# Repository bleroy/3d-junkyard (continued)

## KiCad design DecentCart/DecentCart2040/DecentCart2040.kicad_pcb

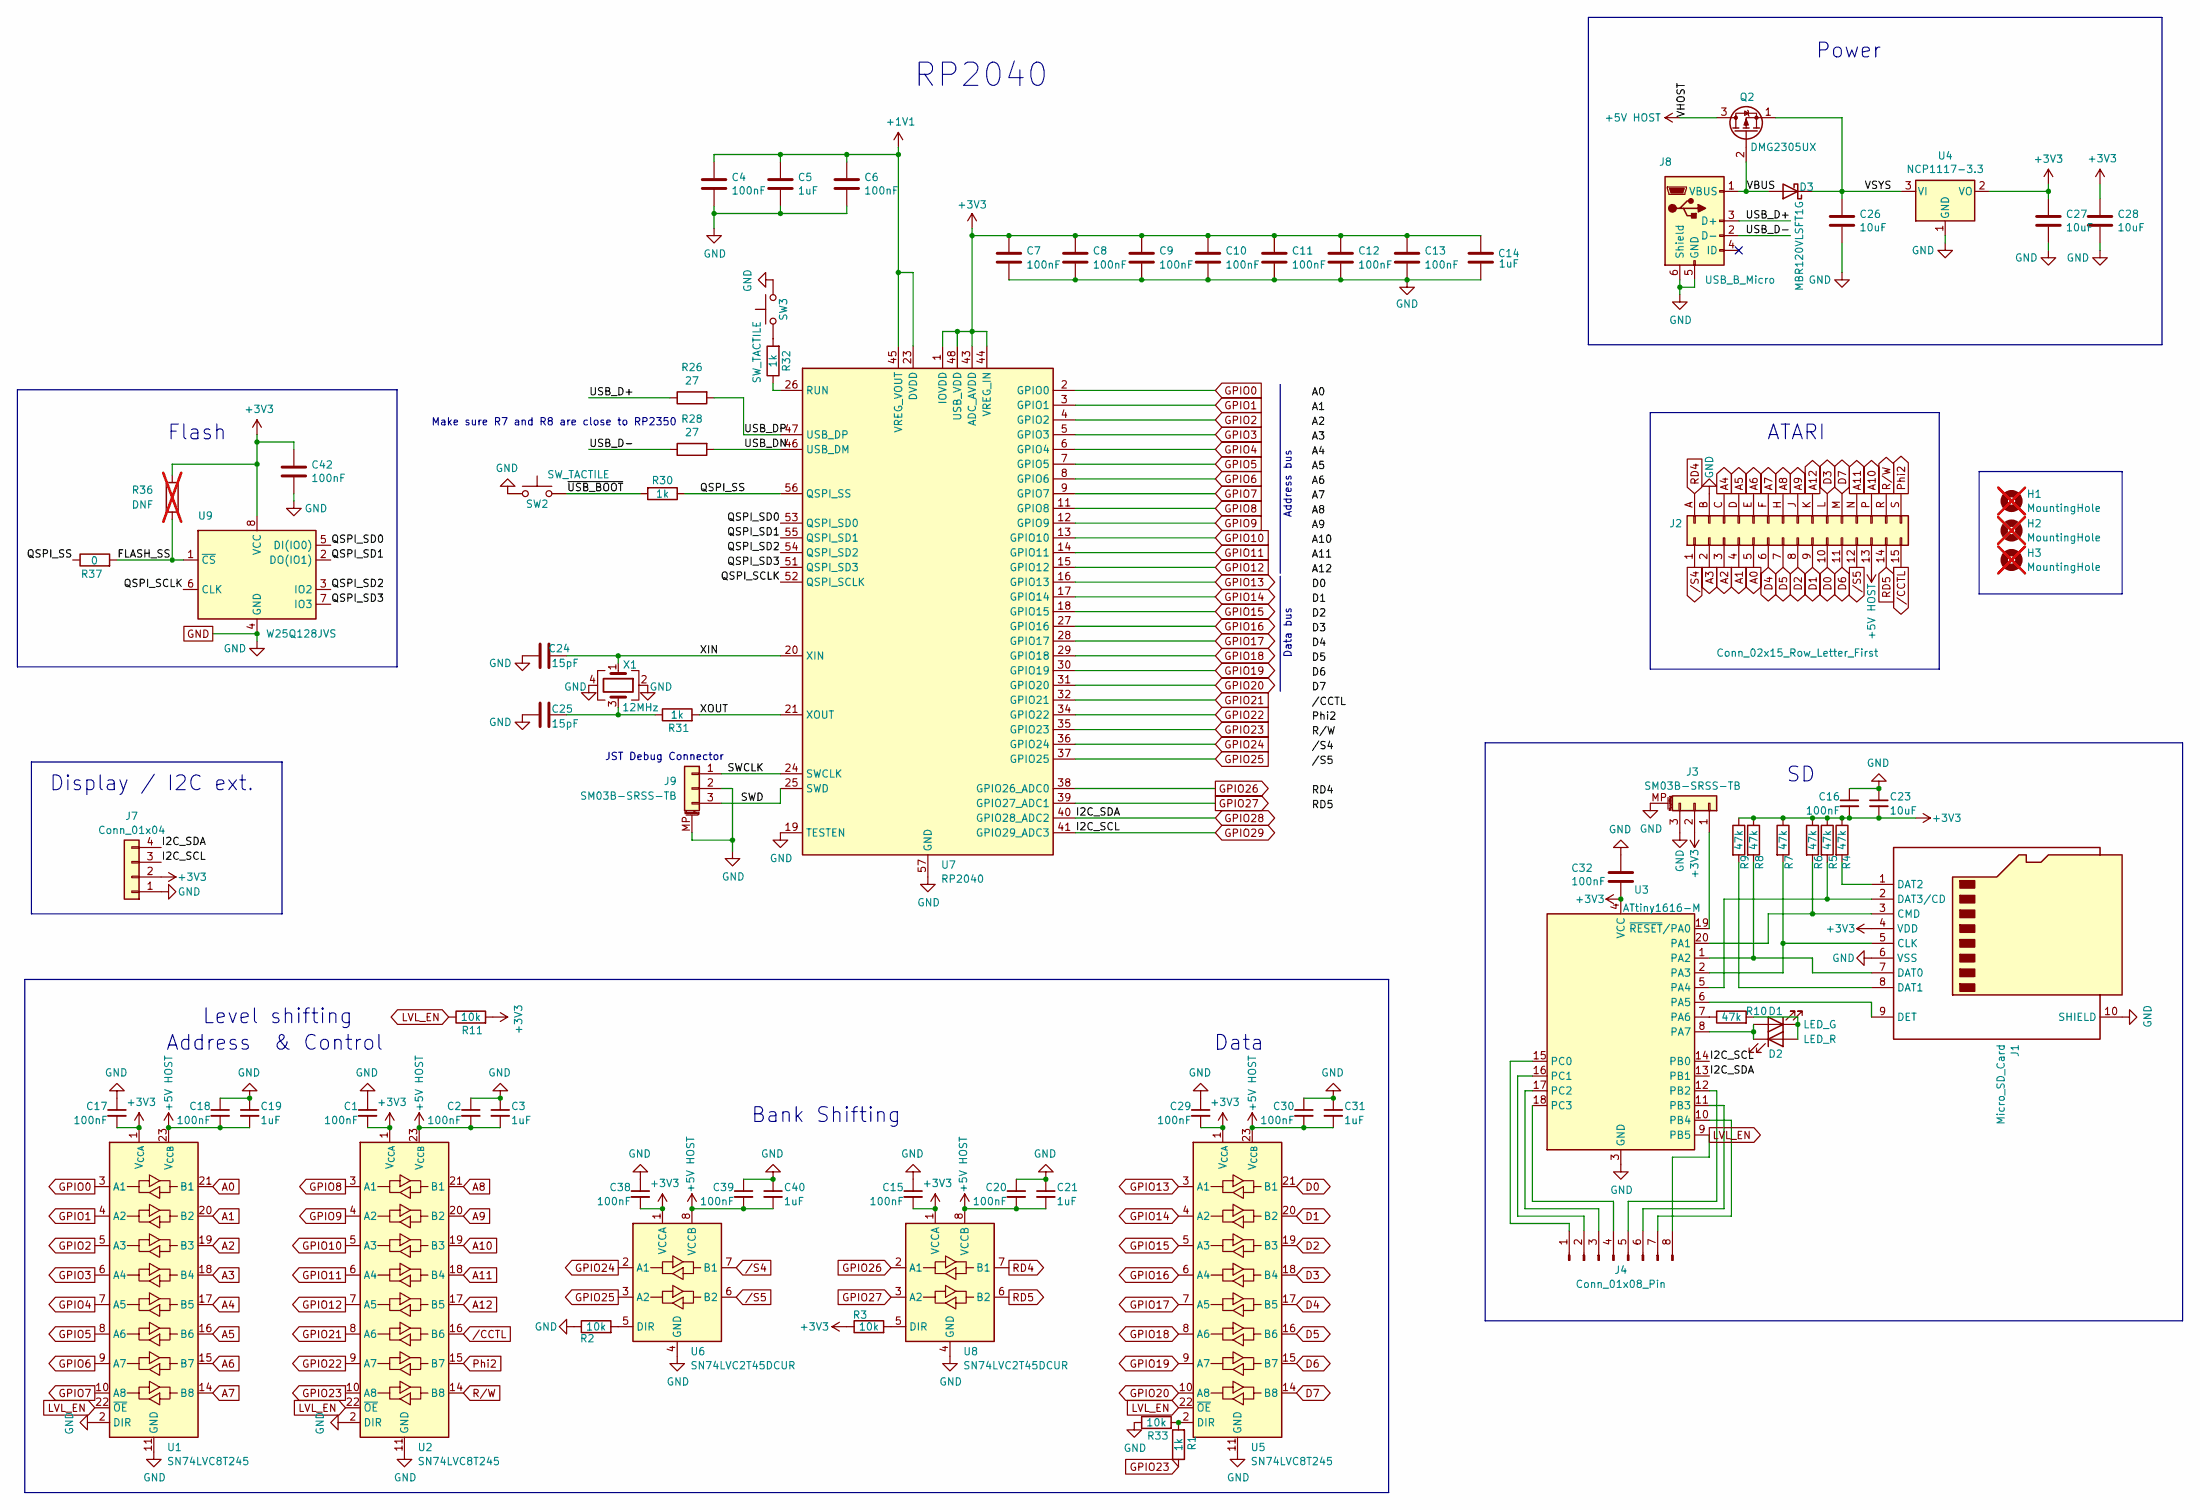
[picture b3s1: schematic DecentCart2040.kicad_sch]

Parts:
C1, C2, C4, C6, C7, C8, C9, C10, C11, C12, C13, C15, C16, C17, C18, C20, C29, C30, C32, C38, C39, C42: 100nF; C_0402_1005Metric; JLCPCB Part # C1525
C3, C5, C14, C19, C21, C31, C40: 1uF; C_0402_1005Metric; JLCPCB Part # C52923
C23, C26, C27, C28: 10uF; C_0402_1005Metric; JLCPCB Part # C15525
C24, C25: 15pF; C_0402_1005Metric; JLCPCB Part # C1548
D1: LED_G; LED_0805_2012Metric; JLCPCB Part # C2297
D2: LED_R; LED_0603_1608Metric; JLCPCB Part # C2286
D3: MBR120VLSFT1G; Nexperia_CFP3_SOD-123W; JLCPCB Part # C223608
H1, H2, H3: MountingHole; MountingHole_2.2mm_M2; not fitted
J1: Micro_SD_Card; Micro SD; JLCPCB Part # C20613191
J2: Conn_02x15_Row_Letter_First; Atari Cartridge Edge Connector
J3, J9: SM03B-SRSS-TB; JST_SH_BM03B-SRSS-TB_1x03-1MP_P1.00mm_Vertical; JLCPCB Part # C160389
J4: Conn_01x08_Pin; PinHeader_2x04_P1.27mm_Vertical
J7: Conn_01x04; OLED_modeule_0_91_128x32_I2C
J8: USB_B_Micro; USB_Micro-B; JLCPCB Part # C2765187
Q2: DMG2305UX; SOT-23; JLCPCB Part # C150470
R1, R30, R31, R32: 1k; R_0402_1005Metric; JLCPCB Part # C11702
R2, R3, R11, R33: 10k; R_0402_1005Metric; JLCPCB Part # C25744
R4, R5, R6, R7, R8, R9, R10: 47k; R_0402_1005Metric; JLCPCB Part # C25792
R26, R28: 27; R_0805_2012Metric; JLCPCB Part # C17561
R36: DNF; R_0402_1005Metric; not fitted
R37: 0; SolderJumper-2_P1.3mm_Bridged_RoundedPad1.0x1.5mm; JLCPCB Part # C2074089
SW2, SW3: SW_TACTILE; Tactile_Switch_Basic_XKB_TS-1187A; JLCPCB Part # C318884
U1, U2, U5: SN74LVC8T245; TSSOP-24_4.4x7.8mm_P0.65mm; JLCPCB Part # C27643
U3: ATtiny1616-M; VQFN-20-1EP_3x3mm_P0.4mm_EP1.7x1.7mm; JLCPCB Part # C507118
U4: NCP1117-3.3; SOT-223-3_TabPin2; JLCPCB Part # C6186
U6, U8: SN74LVC2T45DCUR; VSSOP-8_2.3x2mm_P0.5mm; JLCPCB Part # C15741
U7: RP2040; QFN-56-1EP_7x7mm_P0.4mm_EP3.2x3.2mm; JLCPCB Part # C2040
U9: W25Q128JVS; SOIC-8_5.23x5.23mm_P1.27mm; JLCPCB Part # C97521
X1: 12MHz; Crystal_SMD_Abracon_ABM8AIG-4Pin_3.2x2.5mm; JLCPCB Part # C9002

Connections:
+1V1: C4.1, C5.1, C6.1, U7.23 (DVDD), U7.45 (VREG_VOUT), U7.50 (DVDD)
+3V3: C1.2, C7.1, C8.1, C9.1, C10.1, C11.1, C12.1, C13.1, C14.1, C15.2, C16.2, C17.2, C23.2, C27.1, C28.1, C29.2, C32.2, C38.2, C42.1, J1.4 (VDD), J3.2, J7.2, R3.1, R4.1, R5.1, R6.1, R7.1, R8.1, R9.1, R11.2, R36.1, U1.1 (V_{CCA}), U2.1 (V_{CCA}), U3.4 (VCC), U4.2 (VO), U5.1 (V_{CCA}), U6.1 (VCCA), U7.1 (IOVDD), U7.10 (IOVDD), U7.22 (IOVDD), U7.33 (IOVDD), U7.42 (IOVDD), U7.43 (ADC_AVDD), U7.44 (VREG_IN), U7.48 (USB_VDD), U7.49 (IOVDD), U8.1 (VCCA), U9.8 (VCC)
+5V HOST: C2.2, C3.2, C18.2, C19.2, C20.2, C21.2, C30.2, C31.2, C39.2, C40.2, J2.13, Q2.3 (D), U1.23 (V_{CCB}), U1.24 (V_{CCB}), U2.23 (V_{CCB}), U2.24 (V_{CCB}), U5.23 (V_{CCB}), U5.24 (V_{CCB}), U6.8 (VCCB), U8.8 (VCCB)
/FLASH_SS: R36.2, R37.2, U9.1 (~CS)
/QSPI_SCLK: U7.52 (QSPI_SCLK), U9.6 (CLK)
/QSPI_SD0: U7.53 (QSPI_SD0), U9.5 (DI(IO0))
/QSPI_SD1: U7.55 (QSPI_SD1), U9.2 (DO(IO1))
/QSPI_SD2: U7.54 (QSPI_SD2), U9.3 (IO2)
/QSPI_SD3: U7.51 (QSPI_SD3), U9.7 (IO3)
/QSPI_SS: R30.1, R37.1, U7.56 (QSPI_SS)
/SWCLK: J9.1, U7.24 (SWCLK)
/SWD: J9.3, U7.25 (SWD)
/USB_D+: J8.3 (D+), R26.1
/USB_D-: J8.2 (D-), R28.1
/USB_DN: R28.2, U7.46 (USB_DM)
/USB_DP: R26.2, U7.47 (USB_DP)
/VBUS: D3.2 (A), J8.1 (VBUS), Q2.2 (G)
/XIN: C24.1, U7.20 (XIN), X1.1
/XOUT: R31.2, U7.21 (XOUT)
/~USB_BOOT: R30.2, SW2.2
A0: J2.5, U1.21 (B1)
A1: J2.4, U1.20 (B2)
A2: J2.3, U1.19 (B3)
A3: J2.2, U1.18 (B4)
A4: J2.C, U1.17 (B5)
A5: J2.D, U1.16 (B6)
A6: J2.E, U1.15 (B7)
A7: J2.F, U1.14 (B8)
A8: J2.H, U2.21 (B1)
A9: J2.J, U2.20 (B2)
A10: J2.P, U2.19 (B3)
A11: J2.N, U2.18 (B4)
A12: J2.K, U2.17 (B5)
D0: J2.10, U5.21 (B1)
D1: J2.9, U5.20 (B2)
D2: J2.8, U5.19 (B3)
D3: J2.L, U5.18 (B4)
D4: J2.6, U5.17 (B5)
D5: J2.7, U5.16 (B6)
D6: J2.11, U5.15 (B7)
D7: J2.M, U5.14 (B8)
GND: C1.1, C2.1, C3.1, C4.2, C5.2, C6.2, C7.2, C8.2, C9.2, C10.2, C11.2, C12.2, C13.2, C14.2, C15.1, C16.1, C17.1, C18.1, C19.1, C20.1, C21.1, C23.1, C24.2, C25.1, C26.2, C27.2, C28.2, C29.1, C30.1, C31.1, C32.1, C38.1, C39.1, C40.1, C42.2, J1.6 (VSS), J1.10 (SHIELD), J2.B, J3.3, J3.MP (MountPin), J7.1, J8.5 (GND), J8.6 (Shield), J9.2, J9.MP (MountPin), R2.1, R33.1, SW2.1, SW3.2, U1.2 (DIR), U1.11 (GND), U1.12 (GND), U1.13 (GND), U2.2 (DIR), U2.11 (GND), U2.12 (GND), U2.13 (GND), U3.3 (GND), U3.21 (GND), U4.1 (GND), U5.11 (GND), U5.12 (GND), U5.13 (GND), U6.4 (GND), U7.19 (TESTEN), U7.57 (GND), U8.4 (GND), U9.4 (GND), X1.2, X1.4
GPIO0: U1.3 (A1), U7.2 (GPIO0)
GPIO1: U1.4 (A2), U7.3 (GPIO1)
GPIO2: U1.5 (A3), U7.4 (GPIO2)
GPIO3: U1.6 (A4), U7.5 (GPIO3)
GPIO4: U1.7 (A5), U7.6 (GPIO4)
GPIO5: U1.8 (A6), U7.7 (GPIO5)
GPIO6: U1.9 (A7), U7.8 (GPIO6)
GPIO7: U1.10 (A8), U7.9 (GPIO7)
GPIO8: U2.3 (A1), U7.11 (GPIO8)
GPIO9: U2.4 (A2), U7.12 (GPIO9)
GPIO10: U2.5 (A3), U7.13 (GPIO10)
GPIO11: U2.6 (A4), U7.14 (GPIO11)
GPIO12: U2.7 (A5), U7.15 (GPIO12)
GPIO13: U5.3 (A1), U7.16 (GPIO13)
GPIO14: U5.4 (A2), U7.17 (GPIO14)
GPIO15: U5.5 (A3), U7.18 (GPIO15)
GPIO16: U5.6 (A4), U7.27 (GPIO16)
GPIO17: U5.7 (A5), U7.28 (GPIO17)
GPIO18: U5.8 (A6), U7.29 (GPIO18)
GPIO19: U5.9 (A7), U7.30 (GPIO19)
GPIO20: U5.10 (A8), U7.31 (GPIO20)
GPIO21: U2.8 (A6), U7.32 (GPIO21)
GPIO22: U2.9 (A7), U7.34 (GPIO22)
GPIO23: R1.1, U2.10 (A8), U7.35 (GPIO23)
GPIO24: U6.2 (A1), U7.36 (GPIO24)
GPIO25: U6.3 (A2), U7.37 (GPIO25)
GPIO26: U7.38 (GPIO26_ADC0), U8.2 (A1)
GPIO27: U7.39 (GPIO27_ADC1), U8.3 (A2)
GPIO28: J7.4, U3.13 (PB1), U7.40 (GPIO28_ADC2)
GPIO29: J7.3, U3.14 (PB0), U7.41 (GPIO29_ADC3)
LVL_EN: J4.8, R11.1, U1.22 (~OE), U2.22 (~OE), U3.9 (PB5), U5.22 (~OE)
unnamed: C25.2, R31.1, X1.3
unnamed: D1.2 (A), D2.1 (K), U3.8 (PA7)
unnamed: D1.1 (K), D2.2 (A), R10.2
unnamed: C26.1, D3.1 (K), Q2.1 (S), U4.3 (VI)
unnamed: J1.5 (CLK), R7.2, U3.2 (PA3)
unnamed: J1.3 (CMD), R6.2, U3.20 (PA1)
unnamed: J1.7 (DAT0), R8.2, U3.1 (PA2)
unnamed: J1.8 (DAT1), R9.2
unnamed: J1.1 (DAT2), R4.2
unnamed: J1.2 (DAT3/CD), R5.2, U3.5 (PA4)
unnamed: J1.9 (DET), U3.6 (PA5)
unnamed: J3.1, U3.19 (~RESET/PA0)
unnamed: J4.1, U3.15 (PC0)
unnamed: J4.2, U3.16 (PC1)
unnamed: J4.3, U3.17 (PC2)
unnamed: J4.4, U3.18 (PC3)
unnamed: J4.5, U3.12 (PB2)
unnamed: J4.6, U3.11 (PB3)
unnamed: J4.7, U3.10 (PB4)
unnamed: R32.2, SW3.1
unnamed: R10.1, U3.7 (PA6)
unnamed: R1.2, R33.2, U5.2 (DIR)
unnamed: R2.2, U6.5 (DIR)
unnamed: R32.1, U7.26 (RUN)
unnamed: R3.2, U8.5 (DIR)
Phi2: J2.S, U2.15 (B7)
RD4: J2.A, U8.7 (B1)
RD5: J2.14, U8.6 (B2)
R/W: J2.R, U2.14 (B8)
/CCTL: J2.15, U2.16 (B6)
/S4: J2.1, U6.7 (B1)
/S5: J2.12, U6.6 (B2)

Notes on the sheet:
Flash
RP2040
ATARI
Level shifting
Display / I2C ext.
Address bus
Data bus
Power
Bank Shifting
Make sure R7 and R8 are close to RP2350
Data
JST Debug Connector
Address & Control

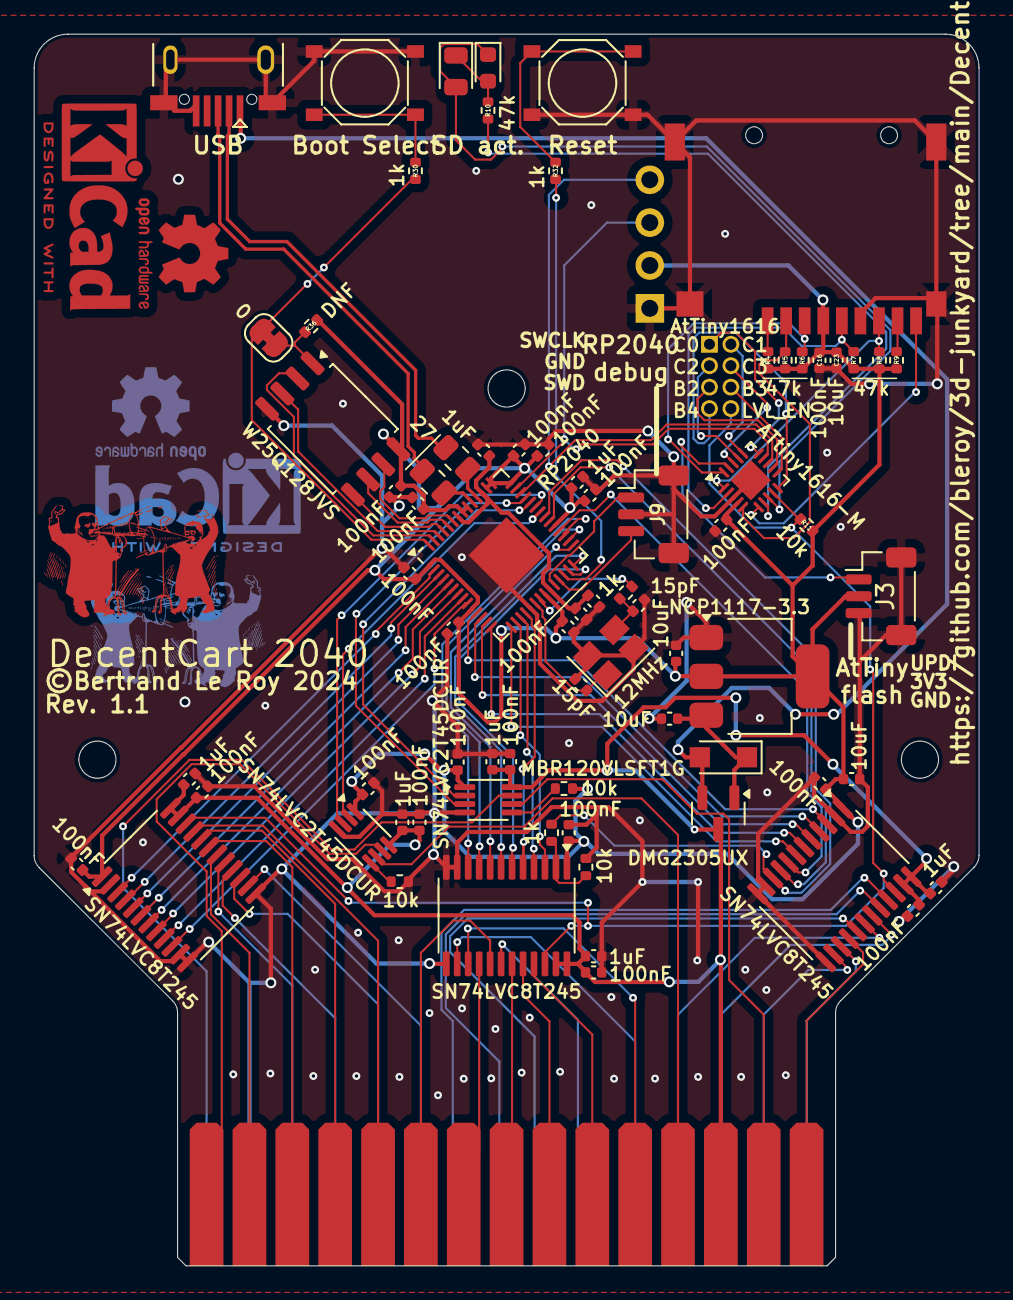
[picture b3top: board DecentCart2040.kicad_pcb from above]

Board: 2 copper layers, 56.0 x 73.0 mm, 80 parts (1 on the bottom side), 105 nets.

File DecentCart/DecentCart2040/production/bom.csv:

Designator,Footprint,Quantity,Value,LCSC Part #
"C1, C10, C11, C12, C13, C15, C16, C17, C18, C2, C20, C29, C30, C32, C38, C39, C4, C42, C6, C7, C8, C9",0402,22,100nF,C1525
"C14, C19, C21, C3, C31, C40, C5",0402,7,1uF,C52923
"C23, C26, C27, C28",0402,4,10uF,C15525
"C24, C25",0402,2,15pF,C1548
D1,0805,1,LED_G,C2297
D2,0603,1,LED_R,C2286
D3,Nexperia_CFP3_SOD-123W,1,MBR120VLSFT1G,C223608
J1,Micro SD,1,Micro_SD_Card,C20613191
"J3, J9",JST_SH_BM03B-SRSS-TB_1x03-1MP_P1.00mm_Vertical,2,SM03B-SRSS-TB,C160389
J4,PinHeader_2x04_P1.27mm_Vertical,1,Conn_01x08_Pin,
J8,USB_Micro-B,1,USB_B_Micro,C2765187
Q2,SOT-23,1,DMG2305UX,C150470
"R1, R30, R31, R32",0402,4,1k,C11702
"R10, R4, R5, R6, R7, R8, R9",0402,7,47k,C25792
"R11, R2, R3, R33",0402,4,10k,C25744
"R26, R28",0805,2,27,C17561
"SW2, SW3",Tactile_Switch_Basic_XKB_TS-1187A,2,SW_TACTILE,C318884
"U1, U2, U5",TSSOP-24_4.4x7.8mm_P0.65mm,3,SN74LVC8T245,C27643
U3,VQFN-20-1EP_3x3mm_P0.4mm_EP1.7x1.7mm,1,ATtiny1616-M,C507118
U4,SOT-223-3_TabPin2,1,NCP1117-3.3,C6186
"U6, U8",VSSOP-8_2.3x2mm_P0.5mm,2,SN74LVC2T45DCUR,C15741
U7,QFN-56-1EP_7x7mm_P0.4mm_EP3.2x3.2mm,1,RP2040,C2040
U9,SOIC-8_5.23x5.23mm_P1.27mm,1,W25Q128JVS,C97521
X1,Crystal_SMD_Abracon_ABM8AIG-4Pin_3.2x2.5mm,1,12MHz,C9002
